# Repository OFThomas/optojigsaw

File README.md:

# optojigsaw
Optical Jigsaw outreach demo

In order to produce a DXF autocad schematic we will use FREECAD which is avaliable on the ubuntu repository.

We want to have around 15mm thickness in the perspex waveguides and they should fit on ~150x150mm^2 blocks

Box outline with waveguides inside, 
---------------
|             |
|_____________|
|_____________| 
|             |
|             |
---------------

---------------
|     |  |    |
|     |  |    |
|     |  |    | 
|     |  |    |
|     |  |    |
---------------

We want to be able to tile the squares together to create a maze. We are also including curved sections (not shown here).

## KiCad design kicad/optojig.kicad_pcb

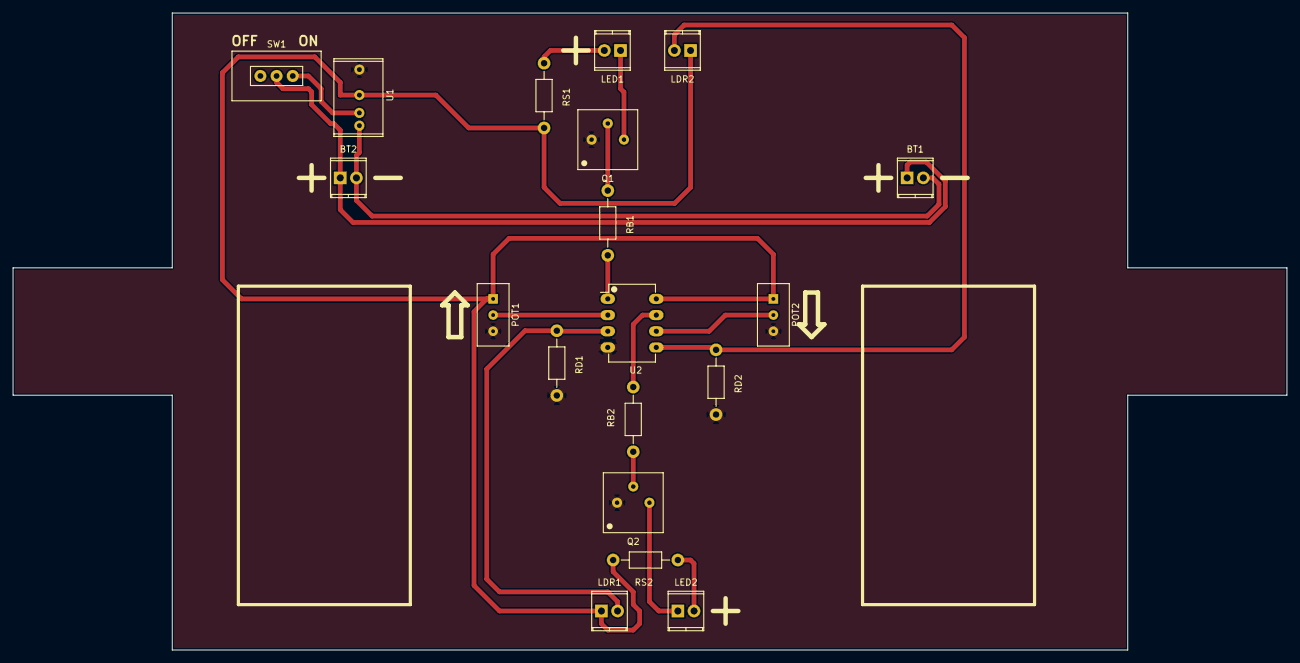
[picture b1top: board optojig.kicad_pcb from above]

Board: 2 copper layers, 200.0 x 100.0 mm, 19 parts (0 on the bottom side), 17 nets.

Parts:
BT1, BT2: Battery_Cell; TerminalBlock_Buchanan_2way
LDR1, LDR2: LDR03; TerminalBlock_Buchanan_2way
LED1: LED; TerminalBlock_Buchanan_2way
LED2: LED2; TerminalBlock_Buchanan_2way
POT1, POT2: POT; Vishay_Trimmer_Through_Hole_2.54mm
Q1, Q2: 2N2219; TO-39
RB1, RB2: 1k; Resistor_Horizontal_RM10mm
RD1, RD2: 680R; Resistor_Horizontal_RM10mm
RS1, RS2: 1k; Resistor_Horizontal_RM10mm
SW1: Switch_SPDT_x2; SPDT_switch
U1: TRN1-0510; TRN_1-0510
U2: LM358; DIP-8_W7.62mm_LongPads

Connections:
GND: POT1.3, POT2.3, Q1.1, Q2.1, RD1.2, RD2.2, U1.5, U2.4
unnamed: BT1.1, BT2.1, SW1.2
unnamed: BT1.2, BT2.2, U1.1
unnamed: LDR1.1, LDR2.1, POT1.1, POT2.1, RS1.2, RS2.2, U1.3, U2.8
unnamed: LDR1.2, RD1.1, U2.3
unnamed: LDR2.2, RD2.1, U2.5
unnamed: LED1.1, Q1.3
unnamed: LED1.2, RS1.1
unnamed: LED2.1, Q2.3
unnamed: LED2.2, RS2.1
unnamed: POT1.2, U2.2
unnamed: POT2.2, U2.6
unnamed: Q1.2, RB1.1
unnamed: Q2.2, RB2.1
unnamed: RB1.2, U2.1
unnamed: RB2.2, U2.7
unnamed: SW1.1, U1.2

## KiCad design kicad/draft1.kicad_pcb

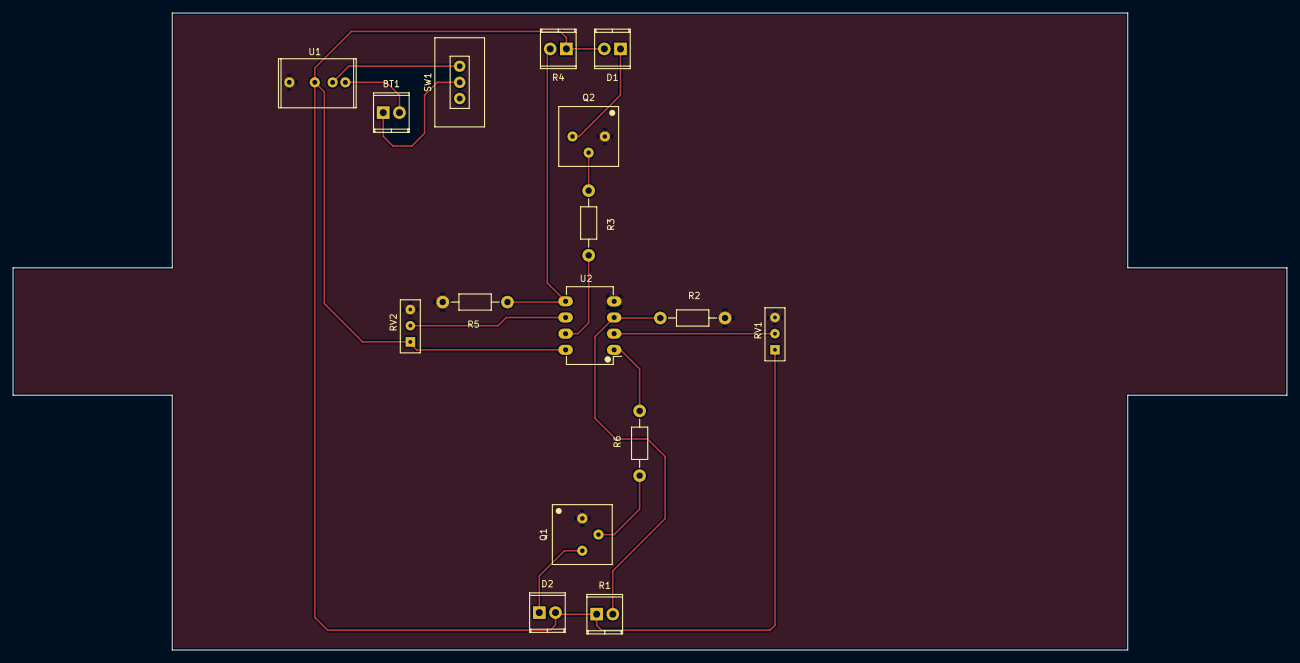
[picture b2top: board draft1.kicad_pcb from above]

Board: 2 copper layers, 200.0 x 100.0 mm, 16 parts (0 on the bottom side), 15 nets.

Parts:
BT1: Battery_Cell; TerminalBlock_Buchanan_2way
D1, D2: LED; TerminalBlock_Buchanan_2way
Q1, Q2: 2N2219; TO-39
R1, R4: LDR03; TerminalBlock_Buchanan_2way
R2, R5: 680R; Resistor_Horizontal_RM10mm
R3, R6: 1k; Resistor_Horizontal_RM10mm
RV1, RV2: POT; Vishay_Trimmer_Through_Hole_2.54mm
SW1: Switch_SPDT_x2; SPDT_switch
U1: TRN1-0510; TRN_1-0510
U2: LM358; DIP-8_W7.62mm_LongPads

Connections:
GND: Q1.1, Q2.1, R2.2, R5.2, RV1.3, RV2.3, U1.5, U2.4
unnamed: BT1.1, SW1.2
unnamed: BT1.2, U1.1
unnamed: D1.1, Q2.3
unnamed: D1.2, D2.2, R1.1, R4.1, RV1.1, RV2.1, U1.3, U2.8
unnamed: D2.1, Q1.3
unnamed: Q1.2, R6.1
unnamed: Q2.2, R3.1
unnamed: R1.2, R2.1, U2.3
unnamed: R3.2, U2.7
unnamed: R4.2, R5.1, U2.5
unnamed: R6.2, U2.1
unnamed: RV1.2, U2.2
unnamed: RV2.2, U2.6
unnamed: SW1.1, U1.2

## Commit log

2018-05-10 Added git script
2018-05-10 Added a test file
2018-05-10 Added template square 150mmx150mm
2018-05-10 Modified test
2018-05-10 Have to close 'tasks' before attempting to commit
2018-05-10 Doesn't save unless you exit editing mode
2018-05-10 Added width to the frame!
2018-05-11 Added an LED datasheet
2018-05-11 Added a phototransistor datasheet
2018-05-13 Added a schematic file and some datasheets for the electronics
2018-05-18 Added PCB layout and datasheets
2018-05-18 Added battery holder datasheet
2018-05-21 Added gerber files zip
2018-05-23 Added final PCB version
2018-06-08 added list to readme
2018-06-08 added to list
2018-06-08 added tuneable resistors to current limit and led brightness control
2018-06-08 added pcb and perspex estimated cost
2018-06-08 Added a datasheet
2018-06-11 Updated repo
2018-08-20 updated readme for new scientist festival
2018-08-20 copied Cheltenham readme
2018-09-14 Added some stuff to the latex doc
